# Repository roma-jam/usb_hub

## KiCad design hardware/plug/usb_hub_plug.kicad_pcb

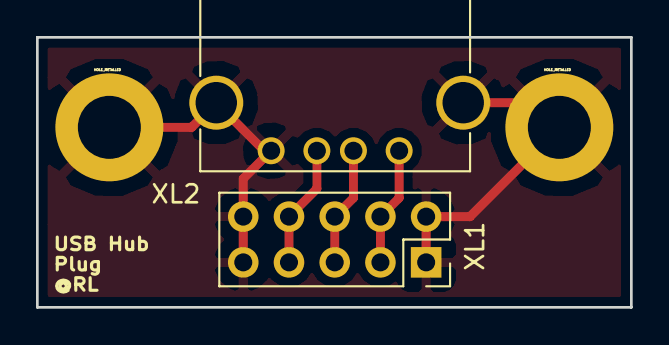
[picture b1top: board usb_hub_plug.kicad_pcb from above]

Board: 2 copper layers, 33.0 x 15.0 mm, 4 parts (0 on the bottom side), 4 nets.

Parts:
HOLE1, HOLE2: HOLE_METALLED; Hole3_5_out6mm
XL1: CONN_10; Socket_Strip_Straight_2x05_Pitch2.54mm
XL2: USB_A

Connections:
+5V: XL1.3, XL1.4, XL2.1
/DM: XL1.5, XL1.6, XL2.2
/DP: XL1.7, XL1.8, XL2.3
GND: HOLE1.H, HOLE2.H, XL1.1, XL1.2, XL1.9, XL1.10, XL2.4, XL2.5

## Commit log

2018-08-17 HW: add usb hub plug PCB
